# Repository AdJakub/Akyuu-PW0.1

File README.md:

# Akyuu PW0.1

My submission for the blueprint project by hackpad! It's a 3x3 macropad with an oled screen and a rotary encoder!
## Features:
- 3x3 key matrix with diodes for NKRO!
- Rotary encoder, firmware defaults it to volume controls
- OLED screen, firmware defaults it to display "Akyuu"
- VIA support for customization

## PCB
Schematic and PCB Made in kicad.
Schematic            |  PCB
:-------------------------:|:-------------------------:
  |  

No errors in DRC, only silkscreen warnings.
## CAD Model:

Nothing special here, just the case from the tutorial.

## Firmware overview
Made in QKM with VIA support. Rotary encoder sends either KC_VOLU or KC_VOLD, and the OLED just displays text. basic stuff.

## BOM
- Seeed xiao rp2040 x1
- Through-hole 1N4148 Diodes x9
- MX-style switches x9
- EC11 rotary encoder x1
- 0.91 inch OLED x1
- keycaps x16
- M3x16mm screws x4
- M3x5mx4mm heatset inserts x4

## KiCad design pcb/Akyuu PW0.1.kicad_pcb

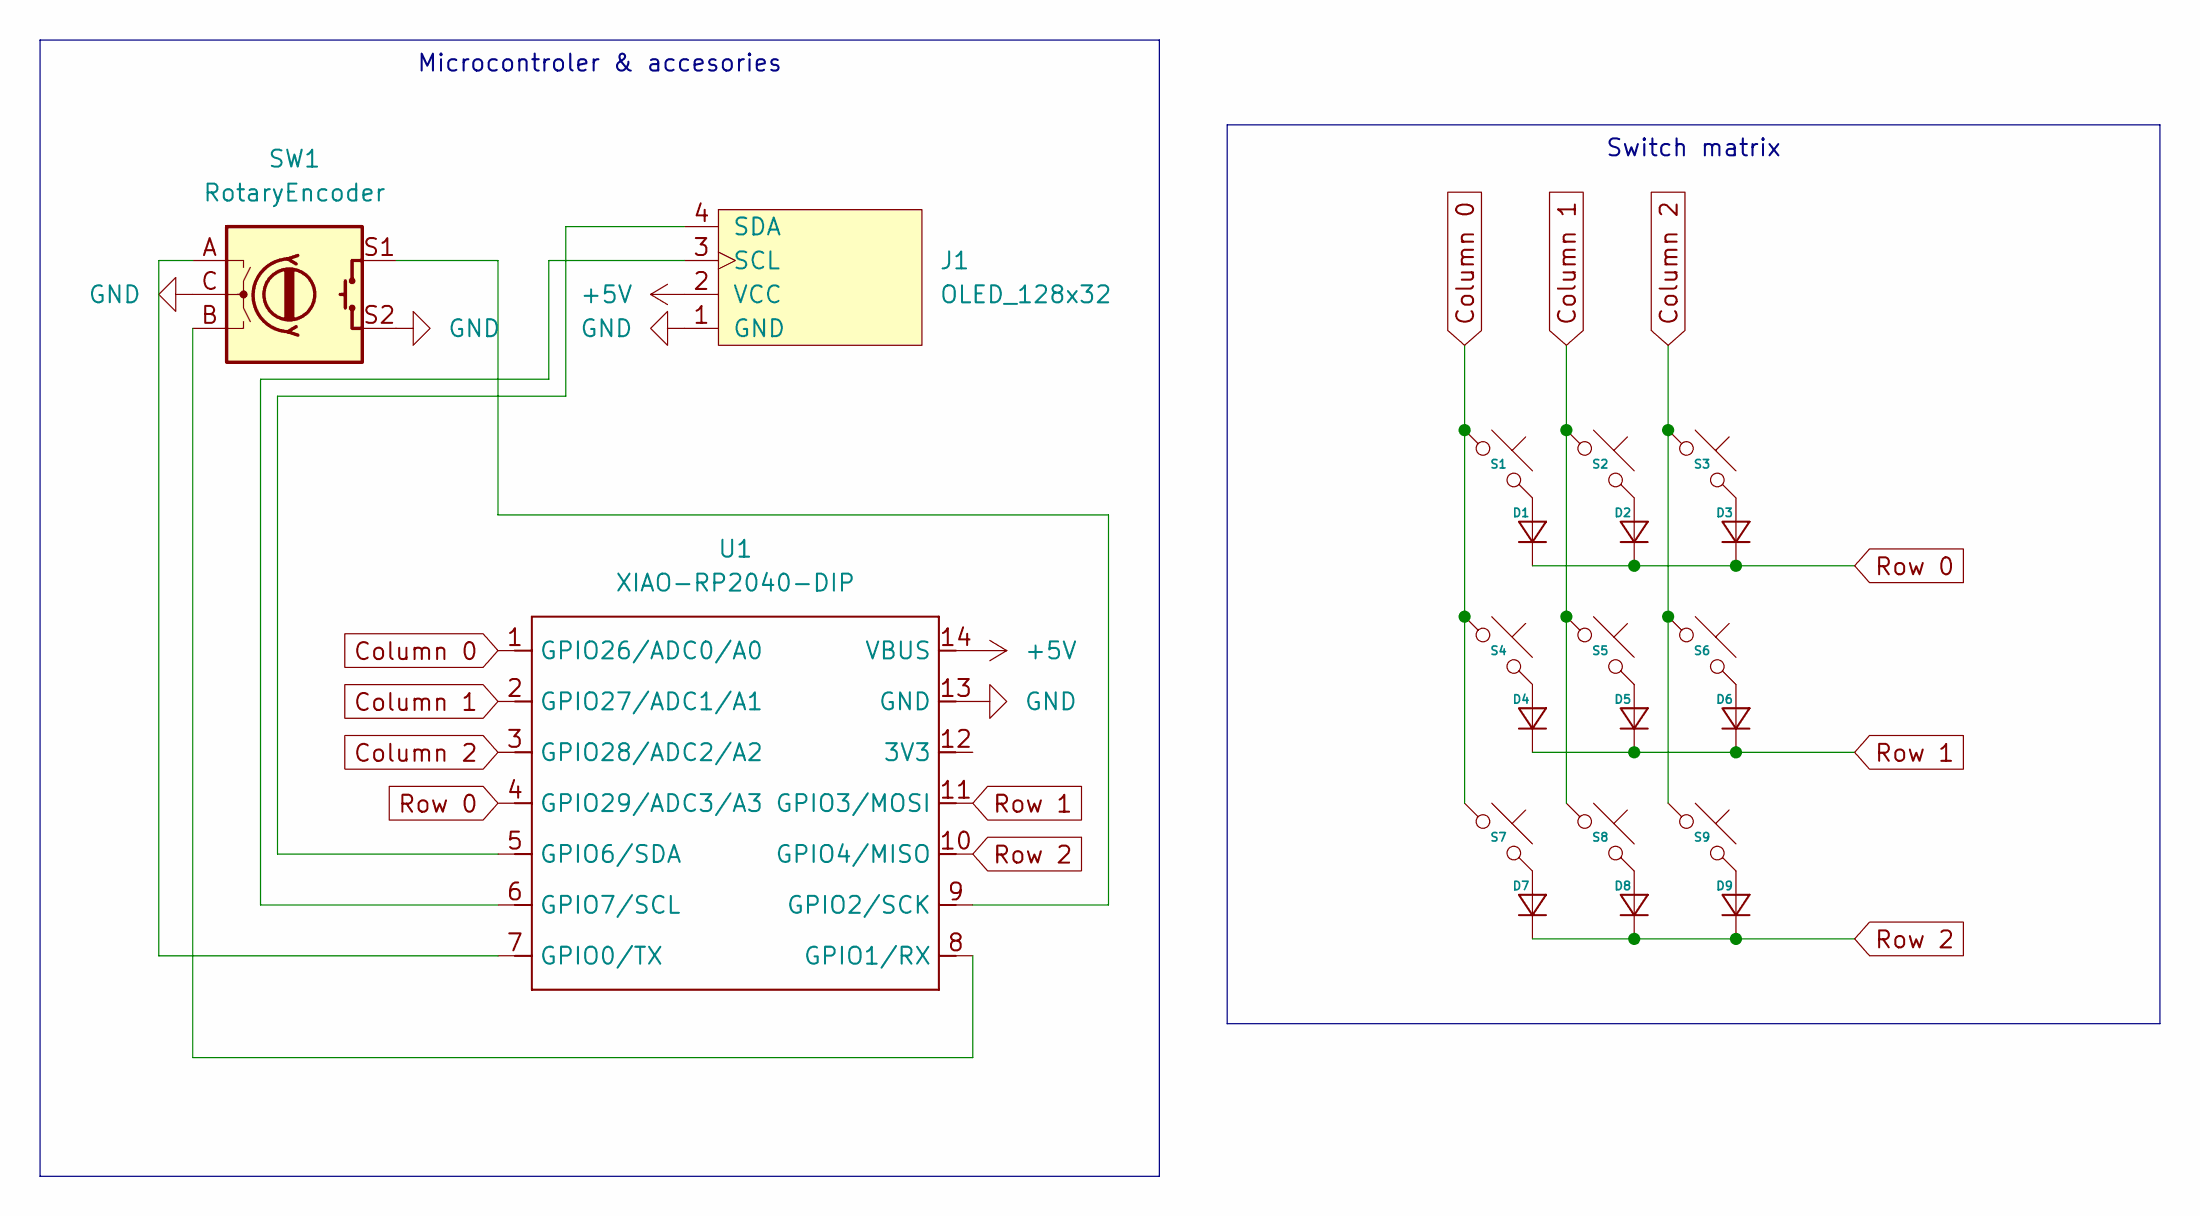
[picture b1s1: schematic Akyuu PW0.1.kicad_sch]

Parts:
D1, D2, D3, D4, D5, D6, D7, D8, D9: D_DO-35_SOD27_P7.62mm_Horizontal
J1: OLED_128x32
S1, S2, S3, S4, S5, S6, S7, S8, S9: SW_Cherry_MX_1.00u_PCB
SW1: RotaryEncoder; Encoder_EC11_MX
U1: XIAO-RP2040-DIP

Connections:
+5V: J1.2 (VCC), U1.14 (VBUS)
Column 0: S1.1, S4.1, S7.1, U1.1 (GPIO26/ADC0/A0)
Column 1: S2.1, S5.1, S8.1, U1.2 (GPIO27/ADC1/A1)
Column 2: S3.1, S6.1, S9.1, U1.3 (GPIO28/ADC2/A2)
GND: J1.1 (GND), SW1.C, SW1.S2, U1.13 (GND)
unnamed: D1.2 (A), S1.2
unnamed: D2.2 (A), S2.2
unnamed: D3.2 (A), S3.2
unnamed: D4.2 (A), S4.2
unnamed: D5.2 (A), S5.2
unnamed: D6.2 (A), S6.2
unnamed: D7.2 (A), S7.2
unnamed: D8.2 (A), S8.2
unnamed: D9.2 (A), S9.2
unnamed: J1.3 (SCL), U1.6 (GPIO7/SCL)
unnamed: J1.4 (SDA), U1.5 (GPIO6/SDA)
unnamed: SW1.A, U1.7 (GPIO0/TX)
unnamed: SW1.B, U1.8 (GPIO1/RX)
unnamed: SW1.S1, U1.9 (GPIO2/SCK)
Row 0: D1.1 (K), D2.1 (K), D3.1 (K), U1.4 (GPIO29/ADC3/A3)
Row 1: D4.1 (K), D5.1 (K), D6.1 (K), U1.11 (GPIO3/MOSI)
Row 2: D7.1 (K), D8.1 (K), D9.1 (K), U1.10 (GPIO4/MISO)

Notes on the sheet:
Switch matrix
Microcontroler & accesories

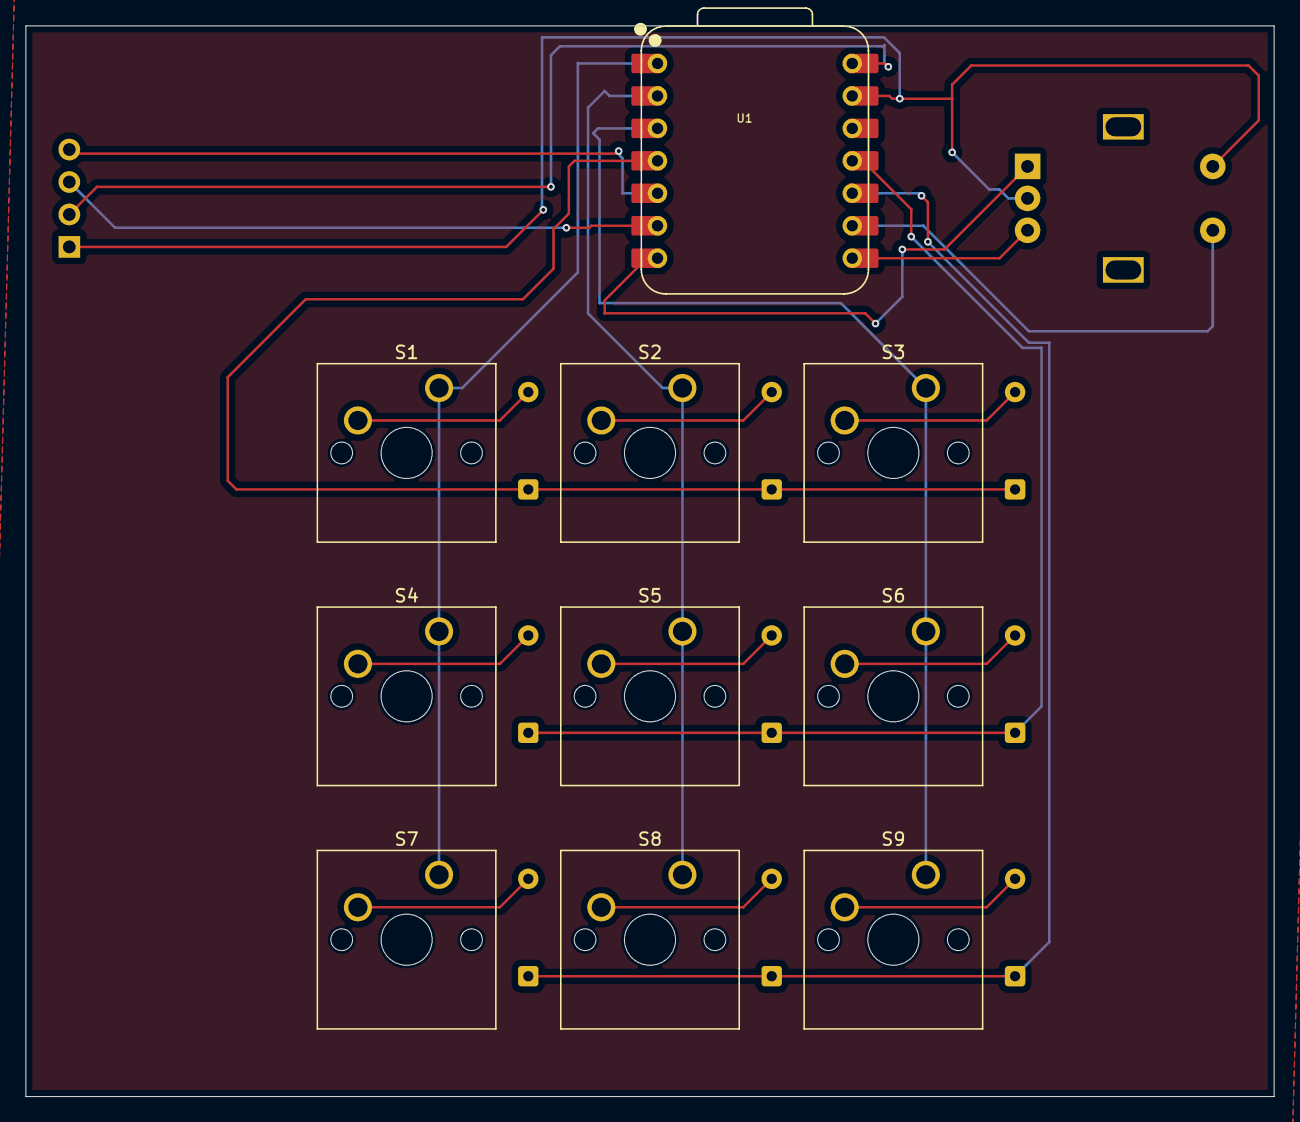
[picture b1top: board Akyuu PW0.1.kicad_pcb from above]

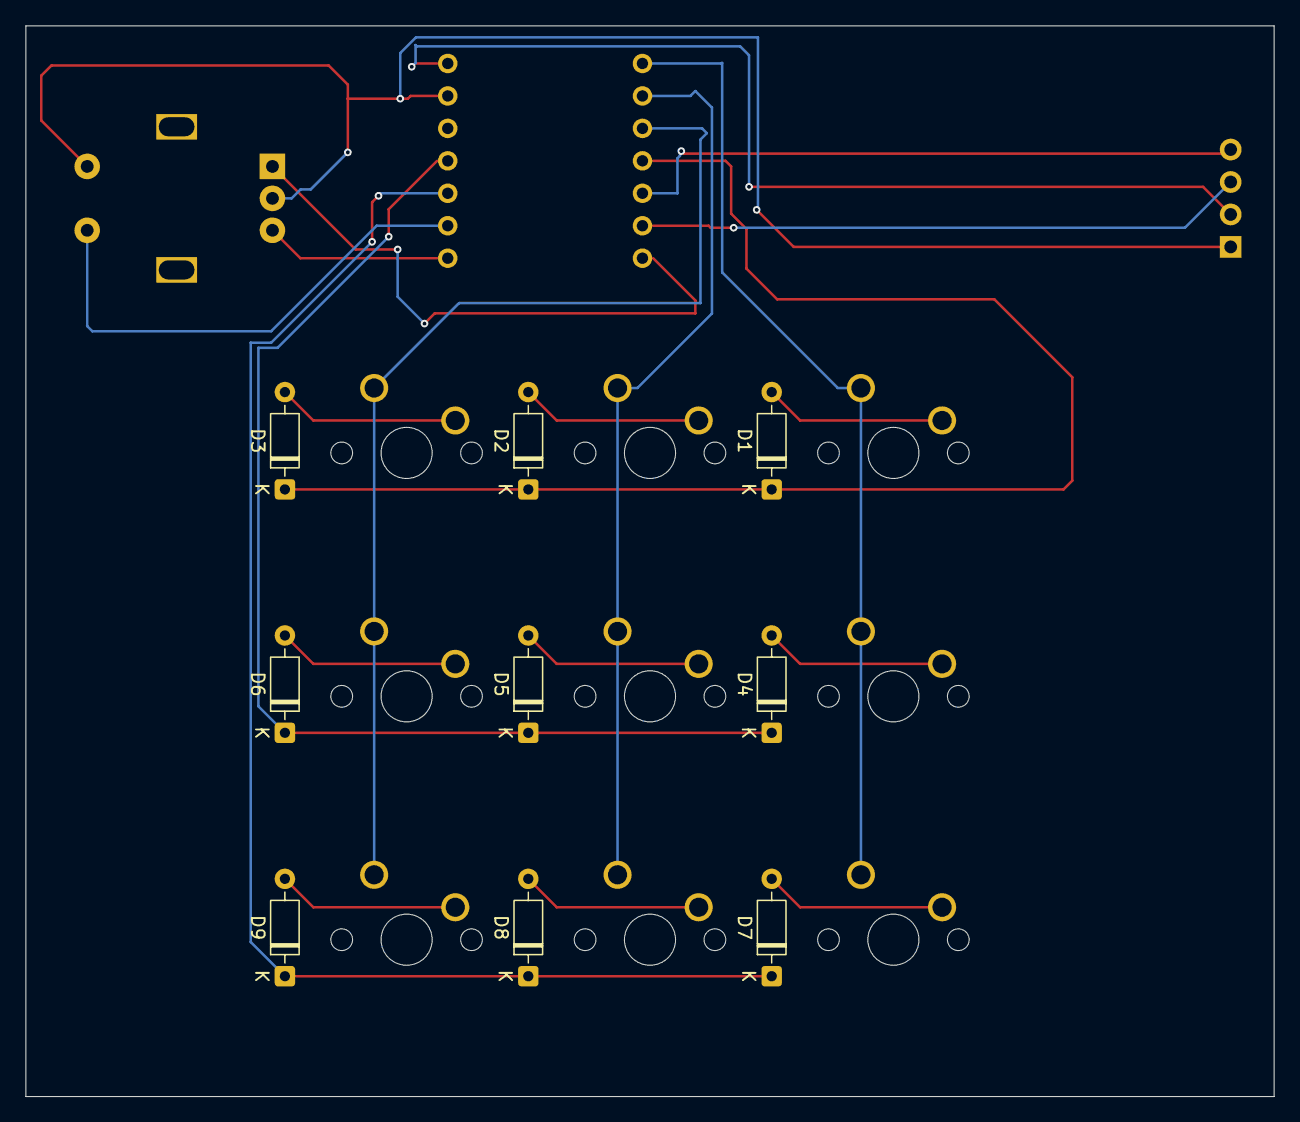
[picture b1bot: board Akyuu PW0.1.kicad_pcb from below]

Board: 2 copper layers, 97.7 x 83.8 mm, 21 parts (9 on the bottom side), 22 nets.

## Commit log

2025-12-30 Create t
